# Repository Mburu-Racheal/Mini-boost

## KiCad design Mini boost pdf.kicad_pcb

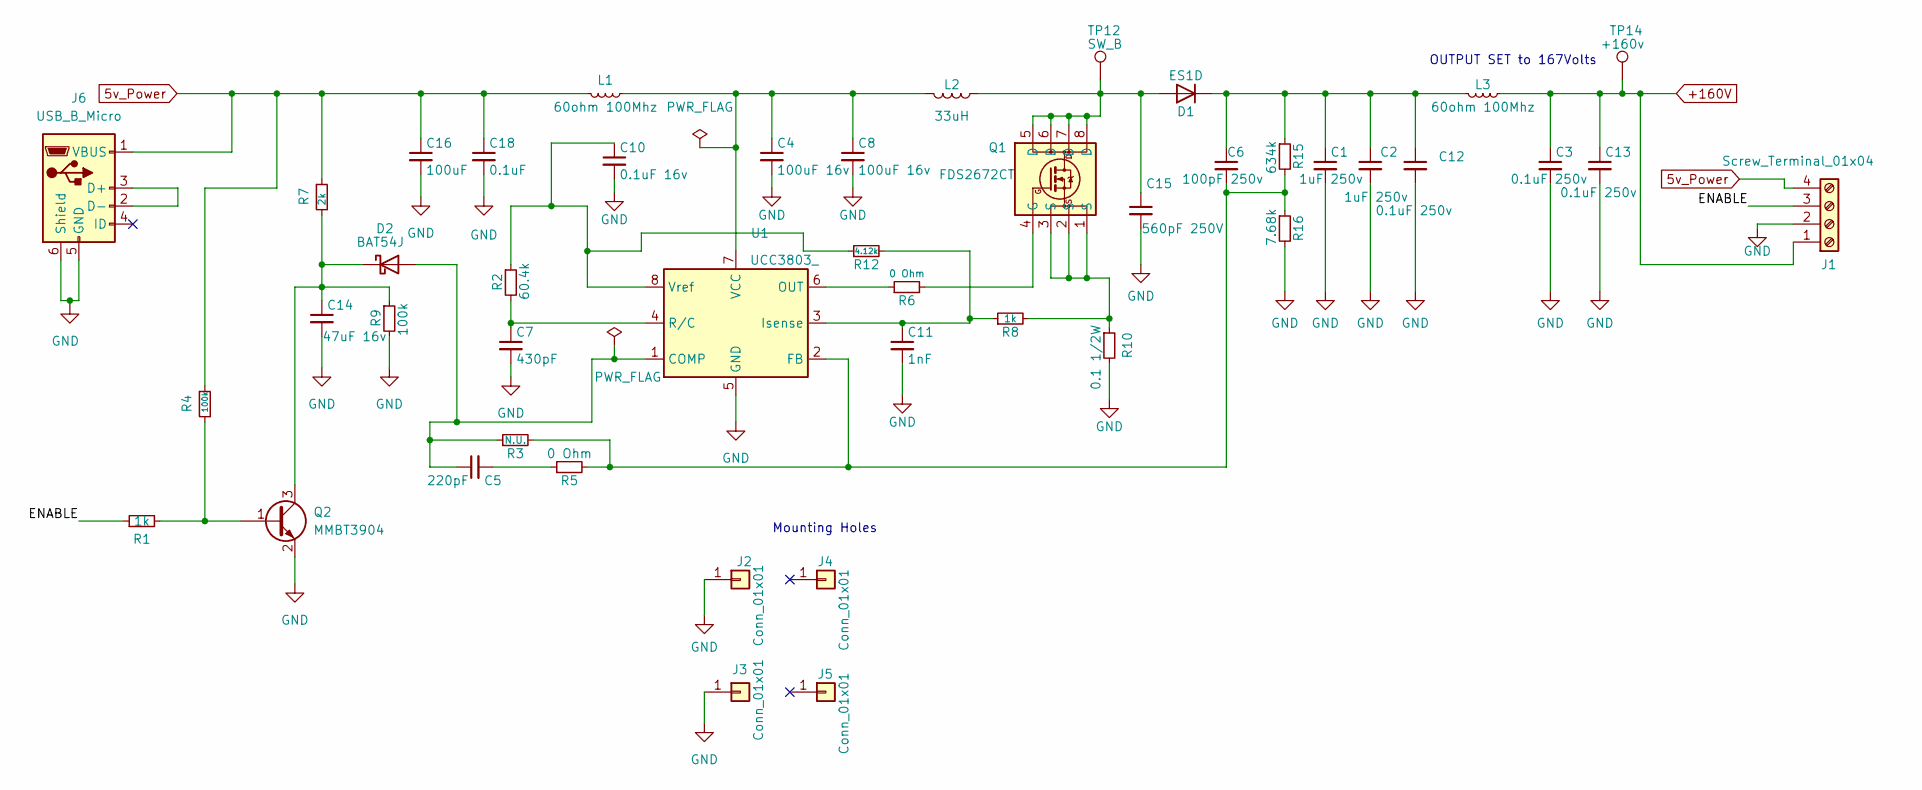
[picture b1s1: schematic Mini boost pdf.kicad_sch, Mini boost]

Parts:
C1, C2: 1uF 250v; C_2220_5650Metric
C3, C12, C13: 0.1uF 250v; C_0805_2012Metric
C4, C8: 100uF 16v; C_1210_3225Metric
C5: 220pF; C_0805_2012Metric
C6: 100pF 250v; C_0805_2012Metric
C7: 430pF; C_0805_2012Metric
C10: 0.1uF 16v; C_0805_2012Metric
C11: 1nF; C_0805_2012Metric
C14: 47uF 16v; C_1206_3216Metric
C15: 560pF 250V; C_0603_1608Metric
C16: 100uF; C_1210_3225Metric
C18: 0.1uF; C_0805_2012Metric
D1: ES1D; D_SMA_Handsoldering
D2: BAT54J; D_SOD-323F
J1: Screw_Terminal_01x04; TerminalBlock_Phoenix_PT-1,5-4-3.5-H_1x04_P3.50mm_Horizontal
J2, J3: Conn_01x01; MountingHole_2.2mm_M2_Pad
J4, J5: Conn_01x01; MountingHole_2.2mm_M2_Pad_Via
J6: USB_B_Micro; USB_Micro-AB_Molex_47590-0001
L1, L3: 60ohm 100Mhz; R_0805_2012Metric
L2: 33uH; L_12x12mm_H6mm
Q1: FDS2672CT; SOIC-8_3.9x4.9mm_P1.27mm
Q2: MMBT3904; SOT-23
R1, R8: 1k; R_0805_2012Metric
R2: 60.4k; R_0805_2012Metric
R3: N.U.; R_0805_2012Metric
R4, R9: 100k; R_0805_2012Metric
R5, R6: 0 Ohm; R_0805_2012Metric
R7: 2k; R_0805_2012Metric
R10: 0.1 1/2W; R_0805_2012Metric
R12: 4.12k; R_0805_2012Metric
R15: 634k; R_0805_2012Metric
R16: 7.68k; R_0805_2012Metric
TP12: SW_B; TestPoint_Pad_D1.0mm
TP14: +160v; TestPoint_Pad_D1.0mm
U1: UCC3803_; SOIC-8_3.9x4.9mm_P1.27mm

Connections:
5v_Power: C16.1, C18.1, J1.4, J6.1 (VBUS), L1.2, R4.1, R7.1
+160V: C3.1, C13.1, J1.1, L3.2, TP14.1
/ENABLE: J1.3, R1.1
GND: C1.2, C2.2, C3.2, C4.2, C7.2, C8.2, C10.2, C11.2, C12.2, C13.2, C14.2, C15.2, C16.2, C18.2, J1.2, J2.1, J3.1, J6.5 (GND), J6.6 (Shield), Q2.2 (E), R9.2, R10.2, R16.2, U1.5 (GND)
unnamed: C1.1, C2.1, C6.1, C12.1, D1.2 (K), L3.1, R15.1
unnamed: C4.1, C8.1, L1.1, L2.2, U1.7 (VCC)
unnamed: C5.1, D2.2 (A), R3.1, U1.1 (COMP)
unnamed: C5.2, R5.1
unnamed: C6.2, R3.2, R5.2, R15.2, R16.1, U1.2 (FB)
unnamed: C7.1, R2.2, U1.4 (R/C)
unnamed: C10.1, R2.1, R12.1, U1.8 (Vref)
unnamed: C11.1, R8.1, R12.2, U1.3 (Isense)
unnamed: C14.1, D2.1 (K), Q2.3 (C), R7.2, R9.1
unnamed: C15.1, D1.1 (A), L2.1, Q1.5 (D), Q1.6 (D), Q1.7 (D), Q1.8 (D), TP12.1
unnamed: J6.2 (D-), J6.3 (D+)
unnamed: Q2.1 (B), R1.2, R4.2
unnamed: R6.1, U1.6 (OUT)
unnamed: Q1.4 (G), R6.2
unnamed: Q1.1 (S), Q1.2 (S), Q1.3 (S), R8.2, R10.1

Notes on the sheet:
Mounting Holes
OUTPUT SET to 167Volts

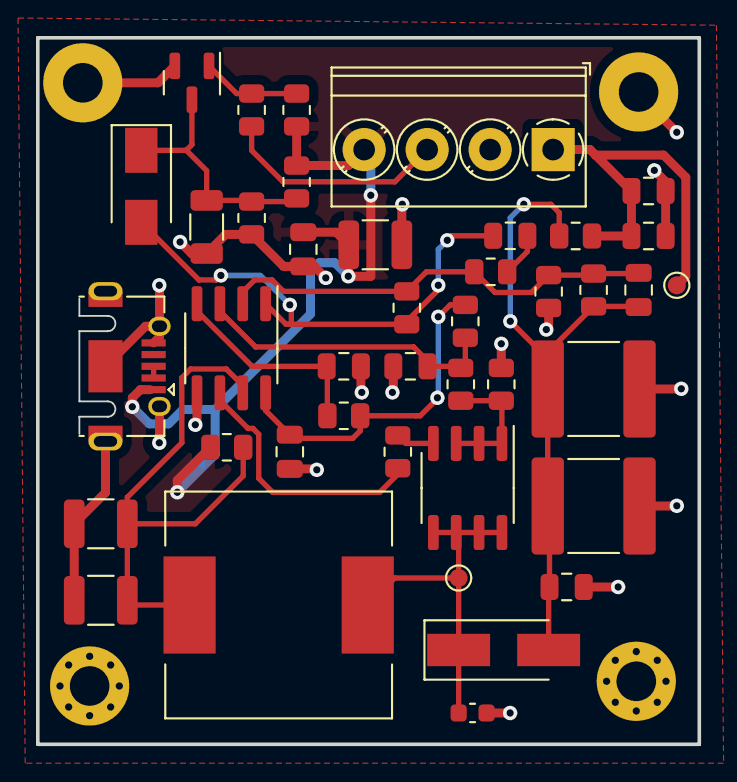
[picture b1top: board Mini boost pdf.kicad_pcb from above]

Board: 2 copper layers, 36.8 x 39.2 mm, 45 parts (0 on the bottom side), 19 nets.
